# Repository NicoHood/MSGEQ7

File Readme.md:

MSGEQ7 Library 1.2.2 + Board v1.0
=================================

The MSGEQ7 library provides an interface to an arbitrary number of MSGEQ7 chips, to convert analog voltage output from the chips to digital data. The data is of values from 0 to 255 (8 bits). Output from each chip, which is input to the library, is referred to in the documentation for this library as a "channel".

The MSGEQ7 is an IC designed to analyze sound (actually, any signal of varying voltages; in the case of sound or music, a signal as from a microphone). The chip measures aspects of input in seven frequency bands, and can provide output related to one (at a time) of these bands as an analog DC voltage signal. The frequency bands the chip analyzes are centered on: 63, 160, 400, 1K, 2.5K, 6.25K, and 16K Hertz.

This repository also includes source information for a [Breakout Board](#breakout-board) with two MSGEQ7 chips. In a case of using two channels of output from a breakout board, referring to one channel as "mono" and two channels as "stereo" makes sense.

#### Features
* IDE 1.6.x with every Arduino compatibly
* [Sparkfun Spectrum Shield](https://www.sparkfun.com/products/13116) compatible
* Reads 1-n MSGEQ7 sensors
* Compact and fast implementation
* More compact and flexible 8 bit resolution
* Optional 10 bit resolution
* Value smoothing
* Tools to reduce noise
* A [Breakout Board](#breakout-board).

#### Examples included:
* Led: blinks led, shows basic usage
* Serial: shows spectrum via serial and how to use more channels
* FastLED: blinks led strip with different frequencies. Shows how to use different syntax.
Uses [FastLED library](https://github.com/FastLED/FastLED)

# Table of Contents
1. [Hardware](#hardware)
  * [Breadboard](#breadboard)
  * [Breakout Board](#breakout-board)
2. [Software](#software)
  * [Library Installation](#library-installation)
  * [API Documentation](#api-documentation)
3. [Contact](#contact)
4. [Version History](#version-history)
5. [License and Copyright](#license-and-copyright)

# Hardware

## Breadboard
To use the MSGEQ7 you first need a few other parts and connect them properly.
Make sure the 33pF capacitor and the 200k Ohm resistor are precise. Otherwise
the frequencies may be off. See the
[data sheet](https://www.sparkfun.com/datasheets/Components/General/MSGEQ7.pdf)
for more information.

Additionally this repository also contains a full instruction of how to build
your own MSGEQ7 [Breakout Board](#breakout-board).

##### Required parts (stereo):
* 2x [MSGEQ7 IC](https://www.sparkfun.com/products/10468)
* 1x [Audio Jack 3.5mm](https://www.sparkfun.com/products/8032)
  (or any other audio input)
* 2x 10nF Capacitor
* 4x 100nF Capacitor
* 2x 33pF Capacitor
* 2x 200k Ohm Resistor
* Led or Led strips
* 1x 220 Ohm Resistor (for Led)

### Breadboard Setup
This would be an example breadboard setup for the Led example.

## Breakout Board
The MSGEQ7 Breakout Board lets you easily hook up an audio source or microphone
to your microcontroller. You may also use a 2nd audio output to pass the audio
signal to music boxes again. You can solder a 6 or 8 pin header to the board and
connect it to a breadboard for example. It is fully open source so you can
create a copy for yourself or modify it.

##### Features:
* Stereo music analyze
* Audio input via 3.5mm Jack
* Additional audio output
* Additional audio in/output via pin header
* Mounting holes
* Breadboard compatible
* Easy to solder (DIP parts)
* [Open Source Hardware](http://www.oshwa.org/definition/)

##### Required parts:
* 1x Breakout Board
* 2x [MSGEQ7 IC](https://www.sparkfun.com/products/10468)
* 2x [Audio Jack 3.5mm](https://www.sparkfun.com/products/8032)
* 8 Pin Header Male
* 2x IC Socket 8 Pins (optional)
* 2x 10nF Capacitor
* 4x 100nF Capacitor
* 2x 33pF Capacitor
* 2x 200k Ohm Resistor

### Files:
You can find all needed files in the [board](extras/board/) folder.
Click view raw to download the PDF files.

### Schematic

### PCB

### Soldering the board
You need to cut off the area around the audio jack a bit first to fit them
better. A knife will work best here. After this just solder all components,
starting with the capacitors and resistors to the IC sockets, the audio jacks
and pin header. Any beginner can do this, no SMD component is used.

# Software

## Library Installation
Install the library as you are used to.
More information can be found [here](http://arduino.cc/en/guide/libraries).

## API Documentation

For a very fast library example see the
[MSGEQ7_LED example](/examples/MSGEQ7_LED/MSGEQ7_LED.ino).

### Create MSGEQ7 Object

Every `CMSGEQ7` instance needs pins passed via template to optimize the code.

The reset and strobe pin can be any digital pin on the board. Those are
connected to each MSGEQ7 IC in parallel. You can input as many analog pins as
you have MSGEQ7 ICs. For example only use a single IC for mono mode, 2 for
stereo or more for surround.

If you want to smooth the readings with the last reading pass 0-255 as
first argument. 0 Will disable smoothing, 255 will take 100% of the previous
value. 191-223 is suggested if smoothing is desired.

**Function Prototype:**
```cpp
template <uint8_t smooth, uint8_t resetPin, uint8_t strobePin
          uint8_t firstAnalogPin, uint8_t ...analogPins>
class CMSGEQ7;
```

**Examples:**
```cpp
// Single MSGEQ7 IC, Smoothing enabled (75%)
CMSGEQ7<191, 6, 4, A0> MSGEQ7;

// Two MSGEQ7 ICs (stereo), Smoothing disabled (0%)
CMSGEQ7<0, 6, 4, A0, A1> MSGEQ7;
```

### Initialize MSGEQ7 ICs
Do whatever is required to initialize the ICs and resets it.

**Function Prototype:**
```cpp
void begin(void);
```

**Example:**
```cpp
void setup() {
  // This will set the ICs ready for reading
  MSGEQ7.begin();
}
```

### Read MSGEQ7 ICs
Basic read function. Reads all channels and saves value inside the buffer. You
can access the buffer with the `get()` function. Up to 400FPS (on 16MHz) are
possible with 2 channels from what I've measured.

To automatically read every X seconds you may also use the 2nd function. Used
together with the `ReadsPerSecond(f)` makro you can simply pass an FPS interval
to the reading function. The return value tells you if a new reading was made.

**Function Prototypes:**
```cpp
bool read(void);
bool read(const uint32_t interval);
```

**Examples:**
```cpp
#define MSGEQ7_INTERVAL ReadsPerSecond(50)

void loop() {
  // Analyze MSGEQ7 ICs now. Will always return true.
  bool newReading = MSGEQ7.read();

  // Analyze without delay every interval
  bool newReading = MSGEQ7.read(MSGEQ7_INTERVAL);
}
```

### Reset MSGEQ7 ICs
Resets ICs, so they start reading at 0 again. Normally this is **not required**
since it is done in the `read()` function.

**Function Prototype:**
```cpp
void reset(void);
```

**Example:**
```cpp
void loop() {
  // Reset the IC frequently, otherwise it will get out of sync after a while
  MSGEQ7.reset();
}
```

### Get MSGEQ7 ICs Frequency
Returns the data of the selected frequency and channel. By default this returns
an `uint8_t` value, for 10bit resolution `uint16_t`. Frequency values should be
0-6 where 0 is the lowest frequency (Bass) and 6 the highest.

Depending on how many analog pins you have attached you can select the channel
here (0-n). You can also leave out the channel variable to get an average value
of all channels.

The output only ranges from 0-255 to save memory and use it easier. You won't
lose much information anyways. If you still want to use 10bit mode see
[makros](#makros)

The IC has a standard noise at about 10-19. You should keep that in mind. Have a
look at the [Map Noise](#map-noise) function to get rid of this.

**Function Prototypes:**
```cpp
MSGEQ7_data_t get(const uint8_t frequency, const uint8_t channel);
MSGEQ7_data_t get(const uint8_t frequency);
```

**Examples:**
```cpp
void loop() {
  // Read bass frequency (of all channels)
  uint8_t input = MSGEQ7.get(MSGEQ7_BASS);

  // Read mid frequency (of channel 0)
  uint8_t input = MSGEQ7.get(MSGEQ7_MID, 0);
}
```

### Get MSGEQ7 ICs Volume
Returns the overall volume of all frequencies of a channel. By default this
returns an `uint8_t` value, for 10bit resolution `uint16_t`. The volume however
is **not that useful** actually.

Depending on how many analog pins you have attached you can select the channel
here (0-n). You can also leave out the channel variable to get an average volume
of all channels.

**Function Prototypes:**
```cpp
MSGEQ7_data_t getVolume(uint8_t channel);
MSGEQ7_data_t getVolume(void);
```

**Examples:**
```cpp
void loop() {
  // Read volume (of all channels)
  uint8_t input = MSGEQ7.getVolume();

  // Read volume (of channel 0)
  uint8_t input = MSGEQ7.getVolume(0);
}
```

### Terminate Reading MSGEQ7 ICs
Sets pins to input again to safely remove connections. This is **normally not
required**.

**Function Prototype:**
```cpp
void begin(void);
```

**Example:**
```cpp
void setup() {
  // This will set the ICs pin to input again
  MSGEQ7.end();
}
```

### Map Noise
Normally when using MSGEQ7 you get a background noise of around 15-19 (8bit
mode) even if no music is played. To get rid of this you can use the
`mapNoise()` function to get rid of this. This macro can be used to remap the
input.

You can leave out the last 4 arguments, they will be replaced with default
values. See [makros](#makros) for more information. For 10 bit resolution the
function uses `uint16_t` and 1023 as default maximum value.

**Function Prototype:**
```cpp
inline MSGEQ7_data_t mapNoise(MSGEQ7_data_t x,
                              MSGEQ7_data_t in_min = MSGEQ7_IN_MIN,
                              MSGEQ7_data_t in_max = MSGEQ7_IN_MAX,
                              MSGEQ7_data_t out_min = MSGEQ7_OUT_MIN,
                              MSGEQ7_data_t out_max = MSGEQ7_OUT_MAX);
```

**Example:**
```cpp
void loop() {
  // Remove noise from input
  input = mapNoise(input);
}
```

### Makros
Inside `MSGEQ7.h` some predefined makros are used to make code writing simpler.
You can optionally also enable 10 bit reading mode (0-1024) if you like to.
For most up to date definitions see `MSGEQ7.h` source file.

```cpp
// Software version
#define MSGEQ7_VERSION 121

// Use (optional) full 10 bit analog readings for MSGEQ7
//#define MSGEQ7_10BIT

// FPS makro
#define ReadsPerSecond(f) (1000000UL / (f))

// Basic frequencies definitions (0-6 valid, 7 channels)
#define MSGEQ7_0 0
#define MSGEQ7_1 1
#define MSGEQ7_2 2
#define MSGEQ7_3 3
#define MSGEQ7_4 4
#define MSGEQ7_5 5
#define MSGEQ7_6 6
#define MSGEQ7_BASS 0
#define MSGEQ7_LOW 0
#define MSGEQ7_MID 3
#define MSGEQ7_HIGH 5

// Resolution dependant settings
#ifdef MSGEQ7_10BIT
typedef uint16_t MSGEQ7_data_t;
#define MSGEQ7_IN_MIN 20
#define MSGEQ7_IN_MAX 1023
#define MSGEQ7_OUT_MIN 0
#define MSGEQ7_OUT_MAX 1023
#else
typedef uint8_t MSGEQ7_data_t;
#define MSGEQ7_IN_MIN 20
#define MSGEQ7_IN_MAX 255
#define MSGEQ7_OUT_MIN 0
#define MSGEQ7_OUT_MAX 255
#endif
```

Contact
=======

Contact information can be found here:

www.nicohood.de

Version History
===============
```
1.2.2 Release (16.04.2016)
* Fixed mapNoise() example and keyword #4

1.2.1 Release (05.03.2016)
* Added 1.6.x library schema
* Added board pictures
* Fix reading the wrong frequency over time
* Smooth from 0-255 now
* Fix compiler warnings
* Renamed map function, moved outside the main class
* Improved documentation

1.2 Release (23.04.2015)
* Added breakout board files v1.0
* Optimized performance
* Variable number of ICs readable
* Added optional 10bit resolution
* Added more functions/tools
* Improved examples
* Added MSGEQ7_VERSION definition
* Added library.properties

1.1 Release (10.07.2014)
* Changed syntax
* Optimized performance
* Added more examples

1.0 Release (13.04.2014)
* Added general functionality
```

License and Copyright
=====================
If you use this library for any cool project let me know!

```
Copyright (c) 2014-2016 NicoHood

Permission is hereby granted, free of charge, to any person obtaining a copy
of this software and associated documentation files (the "Software"), to deal
in the Software without restriction, including without limitation the rights
to use, copy, modify, merge, publish, distribute, sublicense, and/or sell
copies of the Software, and to permit persons to whom the Software is
furnished to do so, subject to the following conditions:

The above copyright notice and this permission notice shall be included in
all copies or substantial portions of the Software.

THE SOFTWARE IS PROVIDED "AS IS", WITHOUT WARRANTY OF ANY KIND, EXPRESS OR
IMPLIED, INCLUDING BUT NOT LIMITED TO THE WARRANTIES OF MERCHANTABILITY,
FITNESS FOR A PARTICULAR PURPOSE AND NONINFRINGEMENT. IN NO EVENT SHALL THE
AUTHORS OR COPYRIGHT HOLDERS BE LIABLE FOR ANY CLAIM, DAMAGES OR OTHER
LIABILITY, WHETHER IN AN ACTION OF CONTRACT, TORT OR OTHERWISE, ARISING FROM,
OUT OF OR IN CONNECTION WITH THE SOFTWARE OR THE USE OR OTHER DEALINGS IN
THE SOFTWARE.
```

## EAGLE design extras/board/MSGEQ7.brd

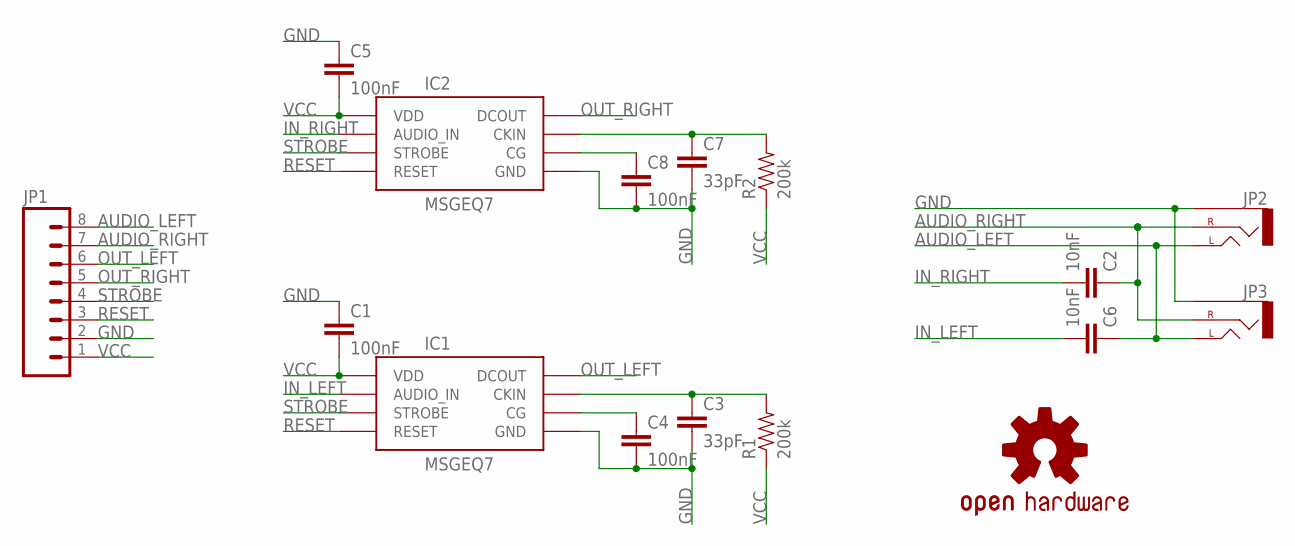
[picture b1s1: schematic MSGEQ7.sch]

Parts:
C1, C4, C5, C8: 100nF; CAP-PTH-SMALL
C2, C6: 10nF; CAP-PTH-SMALL
C3, C7: 33pF; CAP-PTH-SMALL
IC1, IC2: MSGEQ7DIL; DIL-08
JP1: M08SILK_FEMALE_PTH; 1X08
JP2, JP3: AUDIO-JACKPTH; AUDIO-JACK
LOGO1: OSHW-LOGOS; OSHW-LOGO-S
R1, R2: 200k; AXIAL-0.4

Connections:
AUDIO_LEFT: C6.1, JP1.8, JP2.TIP (LEFT), JP3.TIP (LEFT)
AUDIO_RIGHT: C2.1, JP1.7, JP2.RING (RIGHT), JP3.RING (RIGHT)
GND: C1.1, C3.2, C4.2, C5.1, C7.2, C8.2, IC1.2 (GND), IC2.2 (GND), JP1.2, JP2.SLEEVE, JP3.SLEEVE
IN_LEFT: C6.2, IC1.5 (AUDIO_IN)
IN_RIGHT: C2.2, IC2.5 (AUDIO_IN)
unnamed: C8.1, IC2.6 (CG)
unnamed: C7.1, IC2.8 (CKIN), R2.P$2 (2)
unnamed: C3.1, IC1.8 (CKIN), R1.P$2 (2)
unnamed: C4.1, IC1.6 (CG)
OUT_LEFT: IC1.3 (DCOUT), JP1.6
OUT_RIGHT: IC2.3 (DCOUT), JP1.5
RESET: IC1.7 (RESET), IC2.7 (RESET), JP1.3
STROBE: IC1.4 (STROBE), IC2.4 (STROBE), JP1.4
VCC: C1.2, C5.2, IC1.1 (VDD), IC2.1 (VDD), JP1.1, R1.P$1 (1), R2.P$1 (1)

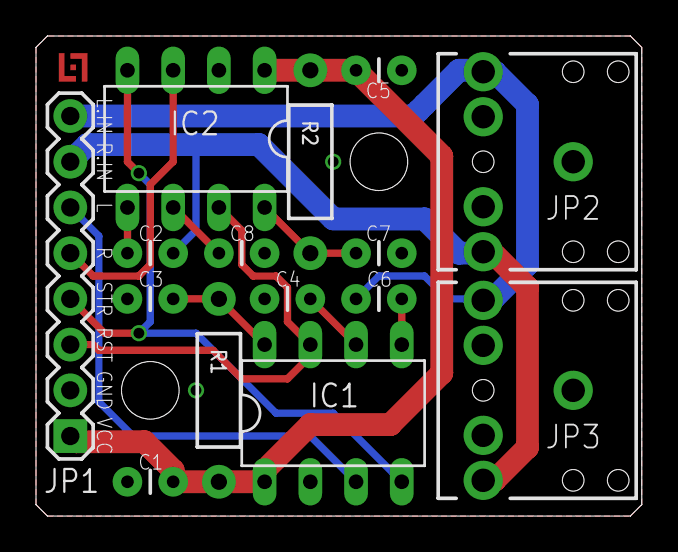
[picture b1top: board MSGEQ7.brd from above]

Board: 2 copper layers, 33.7 x 26.7 mm, 16 parts (0 on the bottom side), 14 nets.

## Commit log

2014-03-08 V1.0 Release of the Library
2014-03-08 Added Led Resistor to the Schematic
2014-03-08 Updated for mono use
2014-03-08 readme update
2014-07-10 readme
2015-03-11 Added board files
2015-03-11 Moved files and updated readme
2015-03-11 Silkscreen fixes
    Moved capacitor name 1 to the top layer, moved IC1 tag a bit up.
    Added images and more pdfs.
2015-03-13 Added PCB preview
2015-03-13 Resized MSGEQ7 Silkscreen
    Also updated the logo on the front to get a bit better PDF with a still
    messed up logo.
2015-03-13 Small Trace update
2015-03-13 Rotated images
2015-04-23 Update 1.2
    Updated Software Library
2015-05-25 Moved files for 1.6.x
2015-05-25 Fixed paths
2015-07-13 Example Updates
2015-10-03 Added Board Pictures
2015-10-03 Minor example improvement
2015-10-03 Improved reading reset(), smooth and map function
2016-03-05 Update Smooth comments
2016-03-05 Minor example fix
2016-04-16 Fix mapNoise() in FastLed example
2016-04-16 Fixed keywords.txt
2016-04-16 Release 1.2.2
2016-04-16 Fixed Serial example
2017-07-05 Updated readme intro
2018-07-14 Remove unused keywords from keywords.txt
    The ReadsPerSecond1 and ReadsPerSecond2 keywords are not used anywhere in the library.
2018-09-22 Added coffee link
2019-11-18 Added support for 12 Bit - Fixed an issue where the audio would return 0 after hitting max value. - Changed resolution of smooth to support 10 and 12 bit smoothing
2019-11-18 changed map to >> .
2019-11-21 Set correct values for smooth - removed confusing comments
2021-01-17 Delete MSGEQ7_Schematic.png
    To add new images of the circuit diagram for this circuit diagram, I deleted the existing one.
2021-01-17 New picture Of Circuit Diagram.
    A new picture of the old circuit diagram is added. A new picture consists of an old design but a new layout with an EasyEDA schematic.

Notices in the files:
parts and their libraries:
SparkFun-Capacitors: Licensing: Creative Commons ShareAlike 4.0 International - https://creativecommons.org/licenses/by-sa/4.0
